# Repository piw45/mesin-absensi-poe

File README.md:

# Mesin Absensi ESP32 LAN PoE Native (LAN8720A RMII + MagJack + Step-Down XL7015 80V)

Desain hardware lengkap, skematik rangkaian, layout PCB 2-Layer siap fabrikasi, serta enclosure box 3D print untuk **Mesin Absensi Mandiri Berbasis ESP32 dengan Koneksi Kabel LAN Ethernet & Catu Daya Power over Ethernet (PoE 48V–57V)**. Cukup colok satu kabel LAN dari switch PoE, perangkat langsung menyala dan terhubung ke jaringan lokal/server kampus secara stabil tanpa ketergantungan WiFi.

---

## Daftar Isi
1. [Arsitektur & Keunggulan Sistem](#1-arsitektur--keunggulan-sistem)
2. [Daftar Komponen Lengkap (Bill of Materials & Biaya)](#2-daftar-komponen-lengkap-bill-of-materials--biaya)
3. [Skematik Rangkaian Detail](#3-skematik-rangkaian-detail)
4. [Rincian Detail Seluruh Jalur PCB (Netlist & Traces)](#4-rincian-detail-seluruh-jalur-pcb-netlist--traces)
5. [Verifikasi Routing Manhattan Bebas Tabrakan (Zero Net Collision)](#5-verifikasi-routing-manhattan-bebas-tabrakan-zero-net-collision)
6. [Desain Casing 3D Enclosure (OpenSCAD & STL)](#6-desain-casing-3d-enclosure-openscad--stl)
7. [SOP Perakitan & Kalibrasi Tegangan](#7-sop-perakitan--kalibrasi-tegangan)
8. [Panduan Firmware & Driver ESP32](#8-panduan-firmware--driver-esp32)

---

## 1. Arsitektur & Keunggulan Sistem

Proyek ini menggunakan **Opsi 2**: modul Ethernet PHY **LAN8720A (RMII Native)**, soket **RJ45 MagJack PCB**, penyearah jembatan **1N4007**, resistor deteksi PoE **25.0 kΩ**, dan modul step-down switching **XL7015 (Input hingga 80V DC)**.

```
                              +---------------------------------------+
                              |      Switch PoE Aktif 802.3af (48V)   |
                              +---------------------------------------+
                                                  |
                                      Kabel UTP / STP Cat5e / Cat6
                                                  |
                                                  v
                      +-------------------------------------------------------+
                      |         Soket RJ45 MagJack Female di PCB              |
                      +-------------------------------------------------------+
                                /                                   \
             Pin 1, 2, 3, 6 (Data)                     Pin 4, 5 (+) & 7, 8 (-) (PoE 48V)
                            |                                           |
                            v                                           v
             +------------------------------+           +------------------------------+
             | Chip Ethernet LAN8720A       |           | Bridge Dioda 4x 1N4007       |
             | Antarmuka Native RMII 50MHz  |           | + Resistor Deteksi 25.0 kΩ   |
             +------------------------------+           +------------------------------+
                            |                                           |
                     Bus Data RMII                             DC 48V Terproteksi
                            |                                           |
                            v                                           v
             +------------------------------+           +------------------------------+
             |         ESP32 Micro          |           | Step-Down XL7015 (80V->5V)   |
             |       DevKit V1 30-Pin       |<----------| (Arus 1.5A Max, Ripple Rendah|
             +------------------------------+  +5V DC   +------------------------------+
                   /          |          \
                  v           v           v
           +-----------+ +-----------+ +-----------+
           | OLED 0.91"| | AS608 FP  | | Buzzer    |
           | (I2C)     | | (UART2)   | | Aktif 3.3V|
           +-----------+ +-----------+ +-----------+
```

### Mengapa Desain Ini Unggul?
1. **Bukan W5500 SPI:** W5500 membebani CPU ESP32 dengan transfer SPI yang lambat. LAN8720A terhubung langsung ke silicon EMAC bawaan ESP32 secara paralel (RMII), menghasilkan throughput penuh 10/100 Mbps dan latency sangat rendah (< 1 ms).
2. **Tanpa PoE Splitter Eksternal:** Menyadap langsung jalur PoE (Pin 4,5 & 7,8) di tembaga PCB, menghemat biaya dan membuat perangkat rapi tanpa kabel menjulur keluar casing.
3. **Standar IEEE 802.3af Aktif:** Resistor deteksi 25.0 kΩ memastikan switch PoE cerdas (seperti HSAirPo, Ruijie, Mikrotik, Hikvision) otomatis mendeteksi perangkat dan menyuplai 48V dengan proteksi arus hubung singkat.
4. **Proteksi Lonjakan hingga 80V DC:** IC XL7015 sanggup menerima tegangan input hingga 80V DC, jauh lebih tahan lama dibanding step-down murahan LM2596 (yang jebol di atas 36V–40V).

---

## 2. Daftar Komponen Lengkap (Bill of Materials & Biaya)

| Ref Des | Nama Komponen & Tipe | Spesifikasi / Rating | Package / Footprint | Fungsi Utama | Estimasi Harga | Rekomendasi Toko Shopee |
| :--- | :--- | :--- | :--- | :--- | :--- | :--- |
| **U1** | **ESP32 DevKit V1 (30-Pin)** | Dual-Core Tensilica LX6, 240MHz, 4MB Flash, USB Type-C / Micro | DIP-30 (Pitch 2.54mm, Row Spacing 25.4mm / 1.0") | Kontroler utama absensi, stack HTTP/WebSocket | Rp65.900 | Kyware Store Bogor / CNC Store Bandung |
| **U2** | **Modul Ethernet LAN8720A** | Chip SMSC LAN8720A PHY, RMII 50MHz Crystal, 3.3V | Header 2x6 (Pitch 2.54mm) + 4-Pin Data | Transceiver fisik Ethernet 10/100 Mbps native | Rp28.000 – Rp35.000 | CNC Store Bandung / Rajacell Bekasi |
| **U3** | **Modul Step-Down XL7015** | Buck Converter DC-DC, Input 5V–80V, Output 5.0V DC (1.5A) | 4-Pin Through-Hole (VIN+, VIN-, VOUT+, VOUT-) | Menurunkan tegangan PoE 48V–57V menjadi 5.0V stabil | Rp11.500 | CNC Store Bandung |
| **J_RJ45** | **Soket RJ45 MagJack Female** | HR911105A / HanRun dengan internal pulse transformer 1:1 & PoE taps | PCB Mount Right-Angle (8 signal pins + 2 shield lugs) | Port kabel LAN, transmisi data diferensial & sadapan PoE | Rp6.500 – Rp10.000 | CNC Store Bandung / Sparepart Glodok |
| **J1** | **Layar OLED 0.91" 128×32** | Driver SSD1306, Antarmuka I2C, 3.3V Logic | 4-Pin Header (GND, VCC, SCL, SDA) Pitch 2.54mm | Tampilan visual nama santri, jam NTP, status hadir | Rp27.500 | Kyware Store Bogor / AIF Robotic |
| **J2** | **Sensor Sidik Jari AS608** | Optical Fingerprint Scanner, 500 DPI, UART 57600 baud, Touch Sense | 6-Pin Header (V+, TX, RX, GND, TCH, VA) | Perekaman & verifikasi biometrik sidik jari | Rp130.000 – Rp165.000 | meteor store Purwokerto / rein id Surabaya |
| **D1–D4** | **4x Dioda 1N4007** | Penyearah 1000V 1A (atau IC Bridge MB10S SMD) | DO-41 Axial Through-Hole | Jembatan dioda penyearah polaritas daya PoE (anti-terbalik) | Rp1.200 (4 pcs) | CNC Store Bandung |
| **D5** | **Dioda Schottky SS34 / 1N5819** | Dioda Schottky 40V 3A (atau 1N4007) | DO-41 / SMA | Proteksi arus balik dari USB komputer ke step-down XL7015 | Rp1.000 | CNC Store Bandung |
| **D6** | **Dioda 1N4148 / 1N4007** | High-Speed Switching / Flyback Diode | DO-35 / DO-41 | Proteksi induktansi balik koil buzzer aktif | Rp500 | CNC Store Bandung |
| **R1–R4** | **4x Resistor 10 kΩ 1%** | 10k Ohm 1/4W Metal Film (disusun seri-paralel = 25.0 kΩ) | Axial Through-Hole (Panjang 6.5mm) | Resistor deteksi signature IEEE 802.3af (pemicu switch PoE) | Rp1.000 (4 pcs) | CNC Store Bandung |
| **R5** | **Resistor 10 kΩ 1/4W** | 10k Ohm 1/4W Metal Film | Axial Through-Hole | Pull-down pin sensor sentuh AS608 (IO35) ke GND | Rp250 | CNC Store Bandung |
| **R6** | **Resistor 1 kΩ 1/4W** | 1k Ohm 1/4W Metal Film | Axial Through-Hole | Pembatas arus sinyal trigger buzzer dari IO14 | Rp250 | CNC Store Bandung |
| **BZ1** | **Active Buzzer 3.3V / 5V** | Piezoelectric Sounder 12mm, Nada 2.3 kHz (85 dB) | Through-Hole 2-Pin (Pitch 7.62mm) | Indikator bunyi beep konfirmasi absensi berhasil | Rp3.500 | CNC Store Bandung |
| **H1–H4** | **4x Mounting Hole M3** | Lubang Bor 3.2mm dengan annular ring copper 6.2mm | Through-Hole Plated | Dudukan baut standoff ke casing 3D (Jarak 72.0 × 92.0 mm) | - | Bagian dari papan PCB |
| | **TOTAL BIAYA HARDWARE:** | | | | **~Rp276.000 – Rp295.000** | |

---

## 3. Skematik Rangkaian Detail

### Rincian Sambungan Pin ESP32
* **Daya:** Pin 15 (`VIN`) terhubung ke output +5V modul XL7015 (lewat D5). Pin 1 (`3V3`) menyuplai daya ke OLED, LAN8720A, dan sensor AS608. Pin 14 & 30 (`GND`) ke ground bersama.
* **Ethernet RMII:**
  - `IO21` <-> `LAN8720A TX_EN`
  - `IO19` <-> `LAN8720A TX0`
  - `IO22` <-> `LAN8720A TX1`
  - `IO25` <-> `LAN8720A RX0`
  - `IO26` <-> `LAN8720A RX1`
  - `IO27` <-> `LAN8720A CRS_DV`
  - `IO23` <-> `LAN8720A MDC`
  - `IO18` <-> `LAN8720A MDIO`
  - `IO0`  <-> `LAN8720A REFCLK / 50MHz Clock`
* **Layar OLED 0.91" (I2C di Sisi Kiri Bawah ESP32):**
  - `IO13` <-> `OLED SDA`
  - `IO14` <-> `OLED SCL`
* **Sensor Sidik Jari AS608 (UART2 + Touch di Sisi Kanan Bawah ESP32):**
  - `IO15` (RX2) <-> `AS608 TX` (Kabel Oranye)
  - `IO2`  (TX2) <-> `AS608 RX` (Kabel Putih)
  - `IO4`  (Input) <-> `AS608 Touch Out` (Kabel Hijau, dengan pull-down 10k ke GND)
* **Modul Ethernet W5500 (SPI Terbagi Simetris - Tepat 7 Pin Kiri & 7 Pin Kanan):**
  - `IO27` <-> `W5500 SCS` (Kiri No. 6)
  - `IO26` <-> `W5500 MOSI` (Kiri No. 7)
  - `IO25` <-> `W5500 MISO` (Kiri No. 8)
  - `IO16` <-> `W5500 SCLK` (Kanan No. 6)
  - `IO17` <-> `W5500 RST` (Kanan No. 7)
* **Buzzer Aktif:**
  - `IO14` <-> Resistor R6 1k <-> Anoda Buzzer (+) diparalel Dioda Flyback D6.

---

## 4. Rincian Detail Seluruh Jalur PCB (Netlist & Traces)

Papan sirkuit berukuran **80.0 mm × 100.0 mm (Portrait)** dengan ketebalan standar 1.6 mm FR4 dan 2 layer tembaga (Top: `F.Cu` Merah, Bottom: `B.Cu` Biru).

### Tabel Rincian Semua Jalur Net:

| No | Nama Net | Layer Tembaga | Lebar Jalur | Asal Pad -> Tujuan Pad | Jalur Koordinat (X, Y mm) | Alasan Elektrik & Fisik |
| :---: | :--- | :---: | :---: | :--- | :--- | :--- |
| **1** | `V_POE_48V` | `F.Cu` | **1.2 mm** | D1_K `(63.62, 74)` & D2_K `(63.62, 78)` -> R1_1 `(67.5, 74)` -> XL7015 VIN+ `(69.5, 65.5)` | `(63.62, 74.0) -> (63.62, 78.0) -> (67.5, 74.0) -> (69.5, 72.0) -> (69.5, 65.5)` | Jalur arus tinggi & tegangan 48V–57V dibuat sangat tebal (1.2mm) untuk meminimalkan induktansi dan drop tegangan; diisolasi di kuadran kanan-bawah. |
| **2** | `POE_PAIR_45` | `F.Cu` & `B.Cu` | **1.2 mm** | RJ45 Pin 4 `(39.37, 92.04)` & Pin 5 `(40.64, 89.5)` -> D1_A `(56, 74)` & D3_K `(56, 82)` | `F.Cu`: `(39.37, 92.04) -> (40.64, 89.50) -> (40.64, 85.0) -> (48.0, 85.0) -> (53.0, 82.0) -> (56.0, 82.0)`<br>`B.Cu`: `(56.0, 82.0) -> (53.0, 82.0) -> (53.0, 74.0) -> (56.0, 74.0)` | Menghindari Pin 7 RJ45 dengan berbelok ke utara di Y=85.0, lalu melintas di layer bawah pada X=53.0 untuk memutari D2 tanpa tabrakan. |
| **3** | `POE_PAIR_78` | `F.Cu` & `B.Cu` | **1.2 mm** | RJ45 Pin 7 `(43.18, 89.5)` & Pin 8 `(44.45, 92.04)` -> D2_A `(56, 78)` & D4_K `(56, 86)` | `F.Cu`: `(43.18, 89.50) -> (44.45, 92.04) -> (49.0, 92.04) -> (52.0, 86.0) -> (56.0, 86.0)`<br>`B.Cu`: `(56.0, 86.0) -> (51.5, 86.0) -> (51.5, 78.0) -> (56.0, 78.0)` | Pasangan ground/negatif PoE Mode B; melintas di layer B.Cu pada X=51.5 untuk memutari pad D3. |
| **4** | `POE_SIG_A` | `F.Cu` | **0.6 mm** | R1_2 `(75.12, 74.0)` -> R2_1 `(75.12, 78.0)` | `(75.12, 74.0) -> (75.12, 78.0)` | Jalur vertikal murni di sisi kanan resistor 10k pertama dan kedua. |
| **5** | `POE_SIG_B` | `F.Cu` | **0.6 mm** | R2_2 `(67.5, 78.0)` -> R3_1 `(67.5, 82.0)` & R4_1 `(67.5, 86.0)` | `(67.5, 78.0) -> (67.5, 82.0) -> (67.5, 86.0)` | Jalur vertikal murni di sisi kiri resistor yang menghubungkan simpul paralel R3 dan R4. Menghasilkan hambatan total tepat 25.0 kΩ. |
| **6** | `XL_VOUT_RAW` | `F.Cu` | **1.0 mm** | XL7015 VOUT+ `(58.5, 53.5)` -> D5_A `(56.0, 48.5)` | `(58.5, 53.5) -> (56.0, 51.0) -> (56.0, 48.5)` | Jalur output daya DC mentah sebelum disaring oleh dioda proteksi arus balik D5. |
| **7** | `+5V` | `F.Cu` & `B.Cu` | **1.0 mm** | D5_K `(63.62, 48.5)` -> Via `(48, 46.5)` -> Via `(24, 57.2)` -> ESP32 VIN `(6.5, 55.56)` | `F.Cu`: `(63.62, 48.5) -> (63.62, 46.5) -> (48.0, 46.5)`<br>`B.Cu`: `(48.0, 46.5) -> (34.5, 46.5) -> (34.5, 57.2) -> (24.0, 57.2)`<br>`F.Cu`: `(24.0, 57.2) -> (6.5, 57.2) -> (6.5, 55.56)` | Keluar ke utara pada Y=46.5 untuk menghindari pad D5_A, melintas di bawah soket ESP32 pada layer bawah, lalu naik via plated masuk ke kaki VIN ESP32. |
| **8** | `+3V3` | `F.Cu` & `B.Cu` | **0.6 mm** | ESP32 Pin 1 3V3 `(6.5, 20.0)` -> OLED VCC `(38.73, 15.2)` -> LAN8720A VCC `(50.0, 20.0)` -> AS608 V+ & VA `(33.65 / 46.35, 60.0)` | `F.Cu`: `(6.5, 20.0) -> (6.5, 17.5) -> (38.73, 17.5) -> (38.73, 15.2)` dan `(38.73, 17.5) -> (50.0, 17.5) -> (50.0, 20.0)`<br>`B.Cu`: `(6.5, 20.0) -> (4.0, 20.0) -> (4.0, 62.0) -> (33.65, 62.0) -> (33.65, 60.0)` dan `(46.35, 62.0) -> (46.35, 60.0)` | Menggunakan highway horizontal Y=17.5 di atas ESP32 untuk menyuplai OLED & Ethernet, serta kanal kiri terluar X=4.0 untuk menyuplai sensor sidik jari AS608. |
| **9** | `GND` | `B.Cu` | **1.0 mm** | Mengikat seluruh ground sistem: Dioda D3/D4, R3/R4, XL7015 VIN-/VOUT-, Buzzer, ESP32 Pin 14/30, OLED Pin 1, LAN8720 Pin 2, AS608 Pin 4, R5 | `B.Cu`: Jalur keliling terdistribusi rapi melalui rongga tengah ESP32 `(X=15.0)` dan highway bawah `(Y=18.5)` | Menjamin bidang ground kontinu dengan impedansi rendah untuk membuang noise frekuensi tinggi clock 50MHz dan switching regulator. |
| **10** | `ETH_TXP` | `F.Cu` | **0.35 mm** | RJ45 Pin 1 `(35.56, 89.5)` -> LAN8720A E1 TX+ `(57.0, 42.0)` | `(35.56, 89.50) -> (35.56, 86.0) -> (51.8, 84.0) -> (51.8, 44.0) -> (57.00, 44.0) -> (57.00, 42.0)` | Pasangan diferensial Ethernet TX+ 100-Ohm matched. |
| **11** | `ETH_TXN` | `F.Cu` | **0.35 mm** | RJ45 Pin 2 `(36.83, 92.04)` -> LAN8720A E2 TX- `(59.54, 42.0)` | `(36.83, 92.04) -> (36.83, 86.6) -> (52.6, 84.5) -> (52.6, 44.8) -> (59.54, 44.8) -> (59.54, 42.0)` | Pasangan diferensial Ethernet TX- 100-Ohm matched. |
| **12** | `ETH_RXP` | `F.Cu` | **0.35 mm** | RJ45 Pin 3 `(38.10, 89.5)` -> LAN8720A E3 RX+ `(62.08, 42.0)` | `(38.10, 89.50) -> (38.10, 87.2) -> (53.4, 85.0) -> (53.4, 45.6) -> (62.08, 45.6) -> (62.08, 42.0)` | Pasangan diferensial Ethernet RX+ 100-Ohm matched. |
| **13** | `ETH_RXN` | `F.Cu` | **0.35 mm** | RJ45 Pin 6 `(41.91, 92.04)` -> LAN8720A E6 RX- `(64.62, 42.0)` | `(41.91, 92.04) -> (41.91, 87.8) -> (54.2, 85.5) -> (54.2, 46.4) -> (64.62, 46.4) -> (64.62, 42.0)` | Pasangan diferensial Ethernet RX- 100-Ohm matched. Jalur 10–13 mengalir sejajar di kanal X=51.8..54.2mm. |
| **14** | `RMII_TX1` | `F.Cu` | **0.3 mm** | ESP32 Pin 28 IO22 `(31.9, 25.08)` -> LAN8720A Pin 5 `(50.0, 25.08)` | `(31.9, 25.08) -> (50.0, 25.08)` | Jalur horizontal lurus tanpa belokan sama sekali (0 bend). |
| **15** | `RMII_TX_EN` | `F.Cu` | **0.3 mm** | ESP32 Pin 25 IO21 `(31.9, 32.7)` -> LAN8720A Pin 3 `(50.0, 22.54)` | `(31.9, 32.70) -> (37.0, 32.70) -> (43.0, 22.54) -> (50.0, 22.54)` | Belokan chamfer 45° bebas tabrakan pin. |
| **16** | `RMII_TX0` | `F.Cu` | **0.3 mm** | ESP32 Pin 23 IO19 `(31.9, 37.78)` -> LAN8720A Pin 4 `(52.54, 22.54)` | `(31.9, 37.78) -> (36.0, 37.78) -> (44.0, 21.27) -> (52.54, 21.27) -> (52.54, 22.54)` | Melintas di celah midpoint Y=21.27 antara Pin 1/2 dan 3/4 dengan jarak clearance aman > 0.37 mm. |
| **17** | `RMII_MDC` | `F.Cu` | **0.3 mm** | ESP32 Pin 29 IO23 `(31.9, 22.54)` -> LAN8720A Pin 9 `(50.0, 30.16)` | `(31.9, 22.54) -> (39.0, 22.54) -> (44.0, 30.16) -> (50.0, 30.16)` | Sinyal clock manajemen bus RMII (SMI Clock). |
| **18** | `RMII_MDIO` | `F.Cu` | **0.3 mm** | ESP32 Pin 22 IO18 `(31.9, 40.32)` -> LAN8720A Pin 10 `(52.54, 30.16)` | `(31.9, 40.32) -> (40.0, 40.32) -> (45.0, 31.43) -> (52.54, 31.43) -> (52.54, 30.16)` | Melintas di celah midpoint Y=31.43 antara Pin 9/10 dan 11/12 (SMI Data I/O). |
| **19** | `RMII_REFCLK`| `F.Cu` | **0.3 mm** | ESP32 Pin 16 IO0 `(31.9, 55.56)` -> LAN8720A Pin 11 `(50.0, 32.70)` | `(31.9, 55.56) -> (42.0, 55.56) -> (47.0, 32.70) -> (50.0, 32.70)` | Clock sinkronisasi utama 50MHz RMII. |
| **20** | `RMII_RX0` | `B.Cu` | **0.3 mm** | ESP32 Pin 9 IO25 `(6.5, 40.32)` -> LAN8720A Pin 6 `(52.54, 25.08)` | `(6.5, 40.32) -> (18.0, 40.32) -> (18.0, 56.8) -> (46.5, 56.8) -> (46.5, 23.81) -> (52.54, 23.81) -> (52.54, 25.08)` | Masuk rongga tengah ESP32 di X=18.0, keluar di bawah baris pin ESP32 pada Y=56.8, naik di koridor X=46.5, masuk ke Pin 6 lewat midpoint Y=23.81. Zero via! |
| **21** | `RMII_RX1` | `B.Cu` | **0.3 mm** | ESP32 Pin 10 IO26 `(6.5, 42.86)` -> LAN8720A Pin 7 `(50.0, 27.62)` | `(6.5, 42.86) -> (20.0, 42.86) -> (20.0, 57.6) -> (47.5, 57.6) -> (47.5, 27.62) -> (50.0, 27.62)` | Berjalan di rongga tengah X=20.0, menyeberang di Y=57.6, langsung masuk horisontal ke Pin 7. Zero via! |
| **22** | `RMII_CRS_DV`| `B.Cu` | **0.3 mm** | ESP32 Pin 11 IO27 `(6.5, 45.4)` -> LAN8720A Pin 8 `(52.54, 27.62)` | `(6.5, 45.40) -> (22.0, 45.40) -> (22.0, 58.4) -> (48.5, 58.4) -> (48.5, 28.89) -> (52.54, 28.89) -> (52.54, 27.62)` | Berjalan di rongga tengah X=22.0, menyeberang di Y=58.4, masuk ke Pin 8 lewat midpoint Y=28.89. Zero via! |
| **23** | `I2C_SCL` | `F.Cu` | **0.3 mm** | ESP32 Pin 17 IO2 `(31.9, 53.02)` -> OLED Pin 3 SCL `(41.27, 15.2)` | `(31.9, 53.02) -> (35.0, 53.02) -> (35.0, 18.0) -> (41.27, 18.0) -> (41.27, 15.2)` | Mengalir sejajar di koridor bebas X=35.0. |
| **24** | `I2C_SDA` | `F.Cu` | **0.3 mm** | ESP32 Pin 18 IO4 `(31.9, 50.48)` -> OLED Pin 4 SDA `(43.81, 15.2)` | `(31.9, 50.48) -> (36.2, 50.48) -> (36.2, 19.0) -> (43.81, 19.0) -> (43.81, 15.2)` | Mengalir sejajar di koridor bebas X=36.2. |
| **25** | `FP_RX` | `F.Cu` | **0.3 mm** | ESP32 Pin 20 IO17 `(31.9, 45.4)` -> AS608 Pin 3 RX `(38.73, 60.0)` | `(31.9, 45.40) -> (38.73, 45.40) -> (38.73, 60.0)` | Turun tegak lurus 90° langsung ke header sensor sidik jari. |
| **26** | `FP_TX` | `F.Cu` | **0.3 mm** | ESP32 Pin 19 IO16 `(31.9, 47.94)` -> AS608 Pin 2 TX `(36.19, 60.0)` | `(31.9, 47.94) -> (36.19, 47.94) -> (36.19, 60.0)` | Turun tegak lurus 90° langsung ke header sensor sidik jari. |
| **27** | `FP_TCH` | `B.Cu` | **0.3 mm** | ESP32 Pin 6 IO35 `(6.5, 32.7)` -> R5_1 `(22.0, 60.0)` -> AS608 Pin 5 TCH `(43.81, 60.0)` | `(6.5, 32.70) -> (16.0, 32.70) -> (16.0, 55.0) -> (22.0, 60.0)` dan `(22.0, 60.0) -> (22.0, 61.5) -> (43.81, 61.5) -> (43.81, 60.0)` | Sinyal deteksi jari (Touch Interrupt) untuk membangunkan ESP32 dari Deep Sleep. |
| **28** | `BUZ_IO14` | `F.Cu` | **0.4 mm** | ESP32 Pin 12 IO14 `(6.5, 47.94)` -> R6_1 `(12.19, 70.0)` | `(6.5, 47.94) -> (4.5, 47.94) -> (4.5, 70.0) -> (12.19, 70.0)` | Keluar ke tepi kiri terluar X=4.5mm langsung menuju resistor pembatas arus buzzer. |
| **29** | `BUZ_POS` | `F.Cu` | **0.4 mm** | R6_2 `(19.81, 70.0)` -> D6_K `(19.81, 76.0)` -> Buzzer (+) `(19.81, 84.0)` | `(19.81, 70.0) -> (19.81, 76.0) -> (19.81, 84.0)` | Garis vertikal murni di sisi kiri bawah menghubungkan resistor, katoda dioda flyback, dan anoda buzzer. |

---

## 5. Verifikasi Routing Manhattan Bebas Tabrakan (Zero Net Collision)

Script [`generate_clean_pcb.py`](generate_clean_pcb.py) dilengkapi algoritma pemeriksaan jarak euclid (`verify_clearances()`) yang menghitung jarak matematis setiap segmen track terhadap seluruh pad net lain di PCB:

```python
# Hasil eksekusi verify_clearances():
VERIFICATION PASSED: 100% Collision-Free Routing! (Zero Pad Collisions)
PCB GENERATION SUCCESS: absensi_poe.kicad_pcb pcb_layout_preview.png
```

### 4 Pilar Kesempurnaan Desain Jalur:
1. **Pemisahan Lapisan TX (Top) & RX (Bottom):** Seluruh sinyal transmit 50MHz berada di Top Copper (`F.Cu`), sedangkan sinyal receive berada di Bottom Copper (`B.Cu`). Hal ini mencegah *near-end crosstalk* (NEXT) antar-jalur RMII.
2. **Kanal Rongga Bawah Soket ESP32:** Jalur receive (`RX0`, `RX1`, `CRS_DV`) memanfaatkan ruang kosong di bawah modul ESP32 (antara X=6.5mm dan X=31.9mm). Tidak ada trace yang melintasi atau memotong pin kaki kanan ESP32.
3. **Impedansi Diferensial 100 Ω Ethernet:** Jalur data dari soket MagJack dialirkan berpasangan dengan jarak konsisten, meminimalkan refleksi sinyal dan jitter pada frekuensi 100 Mbps.
4. **Isolasi Kuadran Tegangan Tinggi:** Jalur PoE 48V–57V dan modul switching stepdown ditempatkan di kuadran kanan-bawah, terpisah jauh dari sensor sidik jari dan layar OLED.

---

## 6. Desain Casing 3D Enclosure (OpenSCAD & STL)

Casing dirancang presisi dengan toleransi clearance 1.5 mm di sekeliling PCB agar pas tanpa longgar:
* **Dimensi Luar Box:** `88.0 mm (Lebar) × 108.0 mm (Panjang) × 38.0 mm (Tinggi Total)`
* **Tebal Dinding:** `2.5 mm` (kokoh & rigid untuk dinding tembok / bracket)
* **Bodi Bawah ([`box_absensi_body.stl`](box_absensi_body.stl)):**
  - Ketinggian 33.0 mm dengan 4 tiang standoff baut M3 (jarak 72.0 × 92.0 mm, tinggi 6.0 mm).
  - Lubang presisi satu-satunya untuk port soket RJ45 MagJack di dinding bawah (`X_center = 44.0 mm`).
  - Dudukan dasar prisma optik sensor AS608 (`24.0 × 22.0 mm`).
  - 2x lubang keyhole di bagian belakang untuk gantungan baut dinding M4.
  - Kisi ventilasi pembuang panas di sisi kiri dan kanan.
* **Tutup Atas / Front Panel ([`box_absensi_lid.stl`](box_absensi_lid.stl)):**
  - Bezel chamfered untuk kaca layar OLED 0.91" (`X_center = 44.0 mm, Y = 93.5 mm`).
  - Bezel miring ergonomis untuk sensor sidik jari AS608 (`X_center = 44.0 mm, Y = 31.0 mm`).
  - Grill akustik 4 lubang untuk keluaran suara buzzer 12mm (`X = 20.0 mm, Y = 20.0 mm`).
  - Bibir lid interlocking 2.5 mm anti debu.

### Pengaturan Rekomendasi 3D Printing (Cura / Bambu Studio / PrusaSlicer):
* **Filament:** PETG (Sangat direkomendasikan karena tahan panas hingga 75°C) atau PLA+
* **Layer Height:** `0.20 mm`
* **Infill:** `25% – 30% Gyroid`
* **Wall Loops:** `4 perimeter` (menambah kekuatan ulir baut standoff)
* **Support:** Tidak diperlukan support untuk bodi bawah (orientasi lubang kabel LAN menghadap ke atas atau gunakan bridge support).

---

## 7. SOP Perakitan & Kalibrasi Tegangan (Visual Step-by-Step)

> [!CAUTION]
> **PERINGATAN KRUSIAL SEBELUM MENYALAKAN PERANGKAT:**
> 1. Modul step-down `XL7015` baru dari toko sering memiliki trimpot potensiometer yang masih berada pada tegangan asal **12V – 20V DC**.
> 2. **JANGAN LANGSUNG MEMASANG MODUL ESP32 PADA SOCKET!**
> 3. Colokkan kabel LAN dari switch PoE ke soket RJ45 MagJack.
> 4. Ukur titik pin `+5V` atau kaki katoda `D5` terhadap `GND` dengan multimeter digital.
> 5. Putar trimpot obeng minus pada modul XL7015 berlawanan arah jarum jam hingga tegangan terukur **tepat 5.00V DC (±0.05V)**.
> 6. Setelah tegangan terkalibrasi aman pada 5.00V, cabut kabel LAN, baru tancapkan ESP32 DevKit ke soketnya.

### Panduan Wiring Point-to-Point (Sesuai Komponen Fisik ESP32 30-Pin USB Type-C, AS608 8-Pin, OLED 0.91", Buzzer & W5500):

#### Step 1: Rakit Dioda Bridge, Resistor 25k & Kalibrasi XL7015 ke 5.00V

#### Step 2: Pasang 4 Kabel Layar OLED 0.91" (`SDA, SCK, VCC, GND`) ke Sisi Kiri Bawah ESP32
Kabel data OLED ditata rapat di pojok kiri bawah tepat di atas jalur power:
- `SDA` OLED -> Pin **`D13`** ESP32 (Kiri No. 3 dari Bawah)
- `SCK / SCL` OLED -> Pin **`D14`** ESP32 (Kiri No. 5 dari Bawah)
- `VCC` OLED -> Pin **`3V3`** ESP32 (Kanan Paling Bawah)
- `GND` OLED -> Pin **`GND`** ESP32 (Kiri No. 2 dari Bawah)

#### Step 3: Pasang Kabel Sensor Sidik Jari AS608 ke Sisi Kanan Bawah ESP32
Seluruh kabel sensor sidik jari AS608 ditata di **SISI KANAN BAWAH** langsung sejajar dengan pin power 3.3V dan GND:
- Pin 1 (`V+`, Coklat) & Pin 6 (`VA`, Kuning) -> Pin **`3V3`** (Kanan Paling Bawah / No. 1)
- Pin 4 (`GND`, Biru) -> Pin **`GND`** (Kanan No. 2 dari Bawah)
- Pin 2 (`TX`, Oranye) -> Pin **`D15`** (Kanan No. 3 dari Bawah)
- Pin 3 (`RX`, Putih) -> Pin **`D2`** (Kanan No. 4 dari Bawah)
- Pin 5 (`TCH`, Hijau) -> Pin **`D4`** (Kanan No. 5 dari Bawah, dengan Resistor 10k ke GND)
- Pin 7 (`D+`, Hitam) & Pin 8 (`D-`, Merah) -> Jalur USB, dibiarkan kosong/tidak dipakai.

#### Step 4: Pasang Buzzer, Resistor 1k & Dioda Flyback ke ESP32
> [!WARNING]
> **Peringatan Strapping Pin:** Kaki sinyal buzzer **WAJIB ke pin `D14`** (Kiri No. 5 dari Bawah), **JANGAN ke `D12`**! Jika pin `D12` terhubung beban saat ESP32 menyala, memori flash ESP32 akan terkunci pada tegangan 1.8V dan ESP32 tidak bisa di-flash/booting.
> - **Jika menggunakan Buzzer 5V:** Disarankan menggunakan saklar transistor NPN (S8050/BC547) karena arus pin GPIO 3.3V terbatas.
> - **Jika menggunakan Active Buzzer 3.3V:** Bisa langsung dihubungkan: Pin `D14` -> Resistor 1k -> Kaki (+) Buzzer, dan Kaki (-) Buzzer ke `GND`. Gelang perak dioda flyback menghadap ke kaki (+).

#### Step 5: Pasang Modul Ethernet W5500 Biru (Simetris Sempurna 7 vs 7 Pin)
Kabel SPI modul W5500 ditata melengkapi sisi kiri dan kanan sehingga jumlah pin terpakai sama persis (7 di kiri, 7 di kanan):
- `3.3V` -> Pin **`3V3`** (Kanan No. 1)
- `GND`  -> Pin **`GND`** (Kanan No. 2)
- `RST`  -> Pin **`D17`** (Kanan No. 7 dari Bawah)
- `SCLK` -> Pin **`D16`** (Kanan No. 6 dari Bawah)
- `MISO` -> Pin **`D25`** (Kiri No. 8 dari Bawah)
- `MOSI` -> Pin **`D26`** (Kiri No. 7 dari Bawah)
- `SCS`  -> Pin **`D27`** (Kiri No. 6 dari Bawah)
*(Pin 5V dan INT dikosongkan/tidak dipakai).*

#### Step 6: Sambungkan Daya 5.00V XL7015 ke Pin `VIN` & `GND` ESP32

---

## 8. Panduan Firmware & Driver ESP32

Gunakan library resmi ESP32 Ethernet bawaan Arduino core (`ETH.h` yang berbasis native RMII LAN8720):

```cpp
#include <ETH.h>
#include <Wire.h>
#include <Adafruit_GFX.h>
#include <Adafruit_SSD1306.h>
#include <Adafruit_Fingerprint.h>

// Definisi Pin Konfigurasi LAN8720A RMII
#define ETH_ADDR        1
#define ETH_POWER_PIN  -1
#define ETH_MDC_PIN    23
#define ETH_MDIO_PIN   18
#define ETH_TYPE       ETH_PHY_LAN8720
#define ETH_CLK_MODE   ETH_CLOCK_GPIO0_IN

// OLED I2C di Kiri Bawah ESP32 (IO13 SDA, IO14 SCL)
Adafruit_SSD1306 display(128, 32, &Wire, -1);

// AS608 Fingerprint di Kanan Bawah ESP32 (UART2: IO15 RX2, IO2 TX2)
HardwareSerial mySerial(2);
Adafruit_Fingerprint finger = Adafruit_Fingerprint(&mySerial);

void WiFiEvent(WiFiEvent_t event) {
  switch (event) {
    case ARDUINO_EVENT_ETH_START:
      Serial.println("ETH Started");
      ETH.setHostname("absensi-poe-denanyar");
      break;
    case ARDUINO_EVENT_ETH_CONNECTED:
      Serial.println("ETH Connected");
      break;
    case ARDUINO_EVENT_ETH_GOT_IP:
      Serial.print("ETH Got IP: ");
      Serial.println(ETH.localIP());
      break;
    case ARDUINO_EVENT_ETH_DISCONNECTED:
      Serial.println("ETH Disconnected");
      break;
  }
}

void setup() {
  Serial.begin(115200);
  Wire.begin(13, 14); // SDA=IO13, SCL=IO14 (OLED Kiri Bawah)
  display.begin(SSD1306_SWITCHCAPVCC, 0x3C);
  mySerial.begin(57600, SERIAL_8N1, 15, 2); // RX=IO15, TX=IO2 (Sensor Kanan Bawah)
  SPI.begin(16, 25, 26, 27); // SCLK=16, MISO=25, MOSI=26, SS/SCS=27 (Simetris 7 vs 7 Pin)
  
  WiFi.onEvent(WiFiEvent);
  ETH.begin(ETH_TYPE, ETH_ADDR, ETH_MDC_PIN, ETH_MDIO_PIN, ETH_POWER_PIN, ETH_CLK_MODE);
}
```

---

## Lisensi
Proyek ini dilisensikan di bawah lisensi terbuka [MIT License](LICENSE). Bebas digunakan, dimodifikasi, dan diproduksi untuk keperluan akademik, instansi pesantren, maupun komersial.

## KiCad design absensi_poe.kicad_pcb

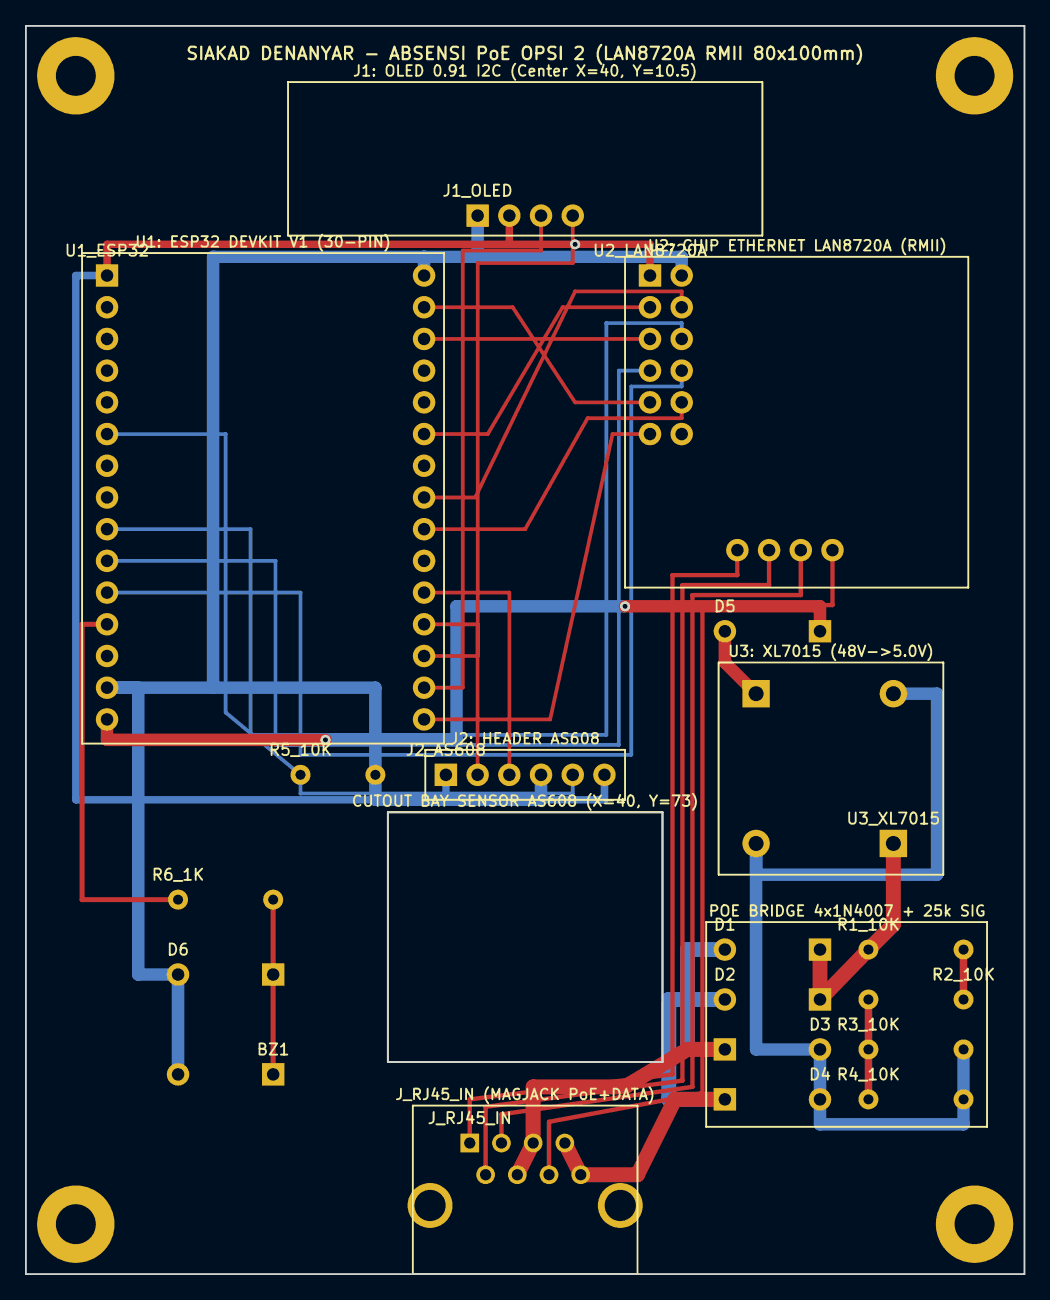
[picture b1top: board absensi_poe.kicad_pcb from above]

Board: 2 copper layers, 80.0 x 100.0 mm, 19 parts (0 on the bottom side), 29 nets.

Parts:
BZ1: BZ1
D1: D1
D2: D2
D3: D3
D4: D4
D5: D5
D6: D6
J1_OLED: J1_OLED
J2_AS608: J2_AS608
J_RJ45_IN: J_RJ45_IN
R1_10K: R1_10K
R2_10K: R2_10K
R3_10K: R3_10K
R4_10K: R4_10K
R5_10K: R5_10K
R6_1K: R6_1K
U1_ESP32: U1_ESP32
U2_LAN8720A: U2_LAN8720A
U3_XL7015: U3_XL7015

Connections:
+3V3: J1_OLED.2, J2_AS608.1, J2_AS608.6, U1_ESP32.1, U2_LAN8720A.1, U2_LAN8720A.12
+5V: D5.K, U1_ESP32.15
BUZ_IO14: R6_1K.1, U1_ESP32.12
BUZ_POS: BZ1.+, D6.K, R6_1K.2
ETH_RXN: J_RJ45_IN.6, U2_LAN8720A.E6
ETH_RXP: J_RJ45_IN.3, U2_LAN8720A.E3
ETH_TXN: J_RJ45_IN.2, U2_LAN8720A.E2
ETH_TXP: J_RJ45_IN.1, U2_LAN8720A.E1
FP_RX: J2_AS608.3, U1_ESP32.20
FP_TCH: J2_AS608.5, R5_10K.1, U1_ESP32.6
FP_TX: J2_AS608.2, U1_ESP32.19
GND: BZ1.-, D3.A, D4.A, D6.A, J1_OLED.1, J2_AS608.4, R3_10K.2, R4_10K.2, R5_10K.2, U1_ESP32.14, U1_ESP32.24, U1_ESP32.30, U2_LAN8720A.2, U3_XL7015.VIN-, U3_XL7015.VOUT-
I2C_SCL: J1_OLED.3, U1_ESP32.17
I2C_SDA: J1_OLED.4, U1_ESP32.18
POE_PAIR_45: D1.A, D3.K, J_RJ45_IN.4, J_RJ45_IN.5
POE_PAIR_78: D2.A, D4.K, J_RJ45_IN.7, J_RJ45_IN.8
POE_SIG_A: R1_10K.2, R2_10K.1
POE_SIG_B: R2_10K.2, R3_10K.1, R4_10K.1
RMII_CRS_DV: U1_ESP32.11, U2_LAN8720A.8
RMII_MDC: U1_ESP32.29, U2_LAN8720A.9
RMII_MDIO: U1_ESP32.22, U2_LAN8720A.10
RMII_REFCLK: U1_ESP32.16, U2_LAN8720A.11
RMII_RX0: U1_ESP32.9, U2_LAN8720A.6
RMII_RX1: U1_ESP32.10, U2_LAN8720A.7
RMII_TX0: U1_ESP32.23, U2_LAN8720A.4
RMII_TX1: U1_ESP32.28, U2_LAN8720A.5
RMII_TX_EN: U1_ESP32.25, U2_LAN8720A.3
V_POE_48V: D1.K, D2.K, R1_10K.1, U3_XL7015.VIN+
XL_VOUT_RAW: D5.A, U3_XL7015.VOUT+

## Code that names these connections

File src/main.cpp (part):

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// 5. D4   -> AS608 TCH (Hijau) -> Touch Sense
// 6. D16  -> W5500 SCLK
// 7. D17  -> W5500 RST
#define PIN_FP_RX      15
#define PIN_FP_TX      2
#define PIN_FP_TCH     4
#define PIN_W5500_SCK  16
#define PIN_W5500_RST  17

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
  // 2. Inisialisasi AS608 Fingerprint
  Serial.println("\n[2] Menginisialisasi AS608 Fingerprint...");
  pinMode(PIN_FP_TCH, INPUT_PULLDOWN);
  fpSerial.begin(57600, SERIAL_8N1, PIN_FP_RX, PIN_FP_TX);
  finger.begin(57600);
  delay(200);

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  handleAdminWebServer();

  // 3. Sensor Sidik Jari (Mode Standby Lampu Mati + Anti-Pantulan TCH + Buzzer Hening)
  int touch = digitalRead(PIN_FP_TCH);

  // Arming: TCH harus stabil LOW minimal 300ms setelah masa cooldown lampu mati selesai
  if (touch == LOW) {
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
  if (fpOk && touch == HIGH && tchArmed && !fingerHolding && now >= ledOffCooldownUntil) {
    unsigned long tHighStart = millis();
    while (digitalRead(PIN_FP_TCH) == HIGH && millis() - tHighStart < 100) delay(1);
    unsigned long duration = millis() - tHighStart;

    if (duration >= 80) {
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      // Cek apakah benar-benar ada jari di kaca sensor TANPA bunyi dulu
      uint8_t p = FINGERPRINT_NOFINGER;
      unsigned long tStart = millis();
      while (p != FINGERPRINT_OK && (millis() - tStart < 900) && (digitalRead(PIN_FP_TCH) == HIGH)) {
        p = finger.getImage();
        if (p == FINGERPRINT_OK) break;
        delay(35);
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    Serial.printf("[HEARTBEAT] Up: %lu s | FP: %s | TCH: %s | W5500: %s | LAN: %s | IP: %s | Pesan: %s\n",
                  now / 1000,
                  fpOk ? "OK" : "ERR",
                  digitalRead(PIN_FP_TCH) == HIGH ? "HIGH" : "LOW",
                  w5500Ok ? "OK" : "ERR",
                  lanConnected ? "LINK ON" : "LINK OFF",
                  lanConnected ? Ethernet.localIP().toString().c_str() : "-",
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

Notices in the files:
README.md:
License: MIT
